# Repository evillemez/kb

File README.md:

This projects contains the definition and build environment for generating a custom keyboard using Ergogen.

* `keyboards/` - each directory here is a separate keyboard meant to be used as input for ergogen. There may be git submodules in some keyboard directories for side-loading ergogen footprints from other places.
* `archive/` - previous attempts at experimenting with possible layouts. Kept for personal reference.  Some use older versions of the ergogen config, are none are expected to be complete or actually work.

## Initial setup

Getting setup initially, you need to do the following:

* initialize submodules recursively, and/or run `make init`
* build the docker container for the general build environment: `make build`
* run the container: `make shell`
* install the ergogen via `yarn` from within the container: `yarn install`

After that, you should be able to run ergogen within the container to build any of the keyboads defined in  `keyboards/`.

## Developing

Use ergogen.cache.works to more easily edit the `config.yml` file in `keyboard/` and see changes.  Just copy/paste them back to commit changes.

To run ergogen locally, connect to the container and run the ergogen command to generate the files:

* `make shell` to connect to container
* Run erogen on any keyboard defined in a subdirectory, or use the makefile shortcut from the root directory: `make gen KB=elv`

Inspect the makefile if you want the see the exact commands and arguments.

## Resources & Prior Art

Major thanks for, and inspiration from the following resources:

* Ergogen:
  * https://ergogen.xyz
  * https://ergogen.cache.works
* Build guide by FlatFootFox: https://flatfootfox.com/ergogen-introduction
* Experiments in automatic build systems & autorouting:
  * https://github.com/soundmonster/samoklava
  * https://github.com/tbaumann/typematrix_split_ergogen
  * https://github.com/ceoloide/corney-island

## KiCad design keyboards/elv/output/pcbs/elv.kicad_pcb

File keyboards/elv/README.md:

My main keyboard: a monoblock split.  Wiring should be roughly the same as a Planck, just slightly different physical layout.

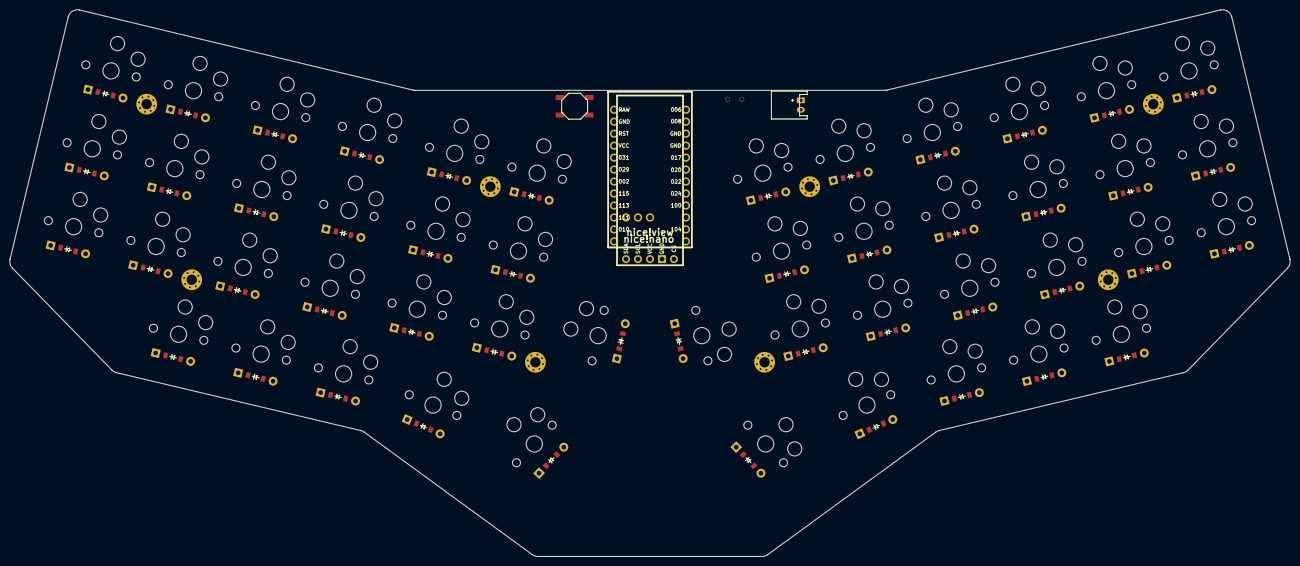
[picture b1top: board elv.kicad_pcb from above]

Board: 2 copper layers, 271.7 x 116.0 mm, 109 parts (0 on the bottom side), 70 nets, no tracks yet.

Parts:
B1: SW_TACT_ALPS_SKQGABE010
D1, D2, D3, D4, D5, D6, D7, D8, D9, D10, D11, D12, D13, D14, D15, D16, D17, D18, D19, D20, D21, D22, D23, D24, D25, D26, D27, D28, D29, D30, D31, D32, D33, D34, D35, D36, D37, D38, D39, D40, D41, D42, D43, D44, D45, D46, D47, D48: ComboDiode
JST1: JST_PH_S2B-PH-K_02x2.00mm_Angled
MCU1: nice_nano
S1, S2, S3, S4, S5, S6, S7, S8, S9, S10, S11, S12, S13, S14, S15, S16, S17, S18, S19, S20, S21, S22, S23, S24, S25, S26, S27, S28, S29, S30, S31, S32, S33, S34, S35, S36, S37, S38, S39, S40, S41, S42, S43, S44, S45, S46, S47, S48: PG1350
T1: SPDT_C128955
_1, _2, _3, _4, _5, _6, _7, _8: MountingHole_2.2mm_M2_Pad_Via
niceView1: niceView; niceView_headers

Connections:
BAT: JST1.1, T1.2
GND: B1.1, JST1.2, MCU1.3, MCU1.4, MCU1.23, niceView1.2
P002: MCU1.18, S7.1, S8.1, S9.1, S21.1, S31.1, S32.1, S33.1, S45.1
P006: MCU1.1, niceView1.5
P008: MCU1.2, niceView1.4
P009: D19.1, D20.1, D21.1, D22.1, D23.1, D24.1, MCU1.13
P010: D1.1, D4.1, D7.1, D10.1, D13.1, D16.1, MCU1.14
P011: D25.1, D28.1, D31.1, D34.1, D37.1, D40.1, MCU1.10
P017: MCU1.5, niceView1.1
P020: MCU1.6, S13.1, S14.1, S15.1, S23.1, S37.1, S38.1, S39.1, S47.1
P022: MCU1.7, S16.1, S17.1, S18.1, S24.1, S40.1, S41.1, S42.1, S48.1
P024: D27.1, D30.1, D33.1, D36.1, D39.1, D42.1, MCU1.8
P029: MCU1.19, S4.1, S5.1, S6.1, S20.1, S28.1, S29.1, S30.1, S44.1
P031: MCU1.20, S1.1, S2.1, S3.1, S19.1, S25.1, S26.1, S27.1, S43.1
P100: D26.1, D29.1, D32.1, D35.1, D38.1, D41.1, MCU1.9
P104: D43.1, D44.1, D45.1, D46.1, D47.1, D48.1, MCU1.11
P111: D2.1, D5.1, D8.1, D11.1, D14.1, D17.1, MCU1.15
P113: D3.1, D6.1, D9.1, D12.1, D15.1, D18.1, MCU1.16
P115: MCU1.17, S10.1, S11.1, S12.1, S22.1, S34.1, S35.1, S36.1, S46.1
RAW: MCU1.24, T1.1
RST: B1.2, MCU1.22
VCC: MCU1.21, niceView1.3
aux_main: D24.2, S24.2
index_bottom: D13.2, S13.2
index_home: D14.2, S14.2
index_top: D15.2, S15.2
inner_bottom: D16.2, S16.2
inner_home: D17.2, S17.2
inner_top: D18.2, S18.2
middle_bottom: D10.2, S10.2
middle_home: D11.2, S11.2
middle_top: D12.2, S12.2
mirror_aux_main: D48.2, S48.2
mirror_index_bottom: D37.2, S37.2
mirror_index_home: D38.2, S38.2
mirror_index_top: D39.2, S39.2
mirror_inner_bottom: D40.2, S40.2
mirror_inner_home: D41.2, S41.2
mirror_inner_top: D42.2, S42.2
mirror_middle_bottom: D34.2, S34.2
mirror_middle_home: D35.2, S35.2
mirror_middle_top: D36.2, S36.2
mirror_mod1_main: D46.2, S46.2
mirror_mod2_main: D45.2, S45.2
mirror_mod3_main: D44.2, S44.2
mirror_mod4_main: D43.2, S43.2
mirror_outer_bottom: D25.2, S25.2
mirror_outer_home: D26.2, S26.2
mirror_outer_top: D27.2, S27.2
mirror_pinky_bottom: D28.2, S28.2
mirror_pinky_home: D29.2, S29.2
mirror_pinky_top: D30.2, S30.2
mirror_primary_main: D47.2, S47.2
mirror_ring_bottom: D31.2, S31.2
mirror_ring_home: D32.2, S32.2
mirror_ring_top: D33.2, S33.2
mod1_main: D22.2, S22.2
mod2_main: D21.2, S21.2
mod3_main: D20.2, S20.2
mod4_main: D19.2, S19.2
outer_bottom: D1.2, S1.2
outer_home: D2.2, S2.2
outer_top: D3.2, S3.2
pinky_bottom: D4.2, S4.2
pinky_home: D5.2, S5.2
pinky_top: D6.2, S6.2
primary_main: D23.2, S23.2
ring_bottom: D7.2, S7.2
ring_home: D8.2, S8.2
ring_top: D9.2, S9.2

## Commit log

2022-10-01 working on outlines
2022-10-01 finished outlines
2022-10-01 more outlines
2022-10-01 added footprints section
2022-10-02 added build env for running ergogen locally in a docker container
2022-10-02 generating pcb without error, but all column nets need adjusting
2022-10-02 improved cutouts by using key binding more heavily instead of rectangles
2022-10-03 refactored main thumb cluster, and thumbfan to fix zone rotation
2022-10-03 added more variants to experiment with overall size
2022-10-04 added 4th attempt, more compact
2022-10-04 only choc hotswap on elv4
2022-10-10 reorg, and added other configs for reference
2022-10-23 added colnets and rownets, and diodes, probably wrong and needs adjustment, unsure
2022-10-24 added todo note for next steps
2022-11-07 added links to readme
2022-11-25 set nets for switches and diodes, added footprint for reset switch
2023-05-10 WIP new layout using ergogen V4 syntax. Previous V3 layout saved as attempts/elv4.yml
2023-05-10 added mirror
2023-05-15 added outlines
2023-06-19 wip, working on footprints, diodes, nets, etc
2023-06-20 test commit from new computer
2023-06-23 added footprints, need to figure out oled, battery, and reset switch
2023-07-23 added updated plank for reference
2023-07-23 added powerswitch and batter footprints
2023-07-23 tweak to dimensions to make slightly more compact
2023-07-23 added ergogen as submodule
2023-07-23 removed submodule
2023-07-23 added personal ergogen fork as submodule
2023-07-23 added infused-kim footprints submodule
2023-07-23 added make command
2023-07-23 ergogen update after installing deps
2023-07-23 updated submodule
2023-07-23 re-added footprint submodule and reorganized repo
2023-07-23 relying on upstream ergogen instead of fork
2023-07-23 added niceview, I think, first pass
2023-07-24 tweaked positions of battery and powerswitch footprints
2023-07-27 replaced ergogen submodule with npm package
2023-07-27 updated readmed
2023-07-27 reduced key padding, tweaked component positions accordingly
2023-07-27 mx spacing on inner keys, choc spacing on outer
2023-07-27 added key matrix nets, still need correct wirings for niceview
2023-07-28 added mirrow row nets
2023-07-29 fixed bad net
2023-07-29 wip multistage docker builds... here there be dragons
2023-07-29 did a thing for niceview based on what Ive found in someone elses repo, not sure that its correct
2023-07-29 new build.sh approach copied and modified from ceoloide , setup and running though not sucessfully routing yet. going with this approach for now
2023-07-29 restore old dockerfile and makefile
2023-07-29 doc updates, wip repo reorg
2023-07-29 added structure for multiple keyboards
2023-07-29 moved keyboard and footprint submodule to new structure
2023-07-29 ergogen running on kb in subdirectory
2023-07-29 added planck reference config for future use
2023-07-29 semi working build script again
2023-07-29 autoroute build script mostly worked on the planck, errors generating images though
2023-07-30 readme
2023-10-21 changed board rotation angle, and made minor resulting position changes to some components
2023-10-21 minor tweak to board rotation
2023-11-19 added nicenano and niceview footprints from another repo
2023-11-19 reworked col and row nets for new nicenano footprint
2023-11-19 added mounting holes in prep for work on case
2023-11-19 installed jscad cli for case generation
2023-11-19 reverted to jscad v1
2023-12-12 reworked nets for easier routing, at least that was the hope
2023-12-17 switched jst and reset footprint locations
2023-12-17 added routed pcbs in routed subdirectory
2023-12-17 stopped ignoring the ergogen output directories
2023-12-17 added ergogen output files
2023-12-17 updated gitignore to exclude kicad cache file
